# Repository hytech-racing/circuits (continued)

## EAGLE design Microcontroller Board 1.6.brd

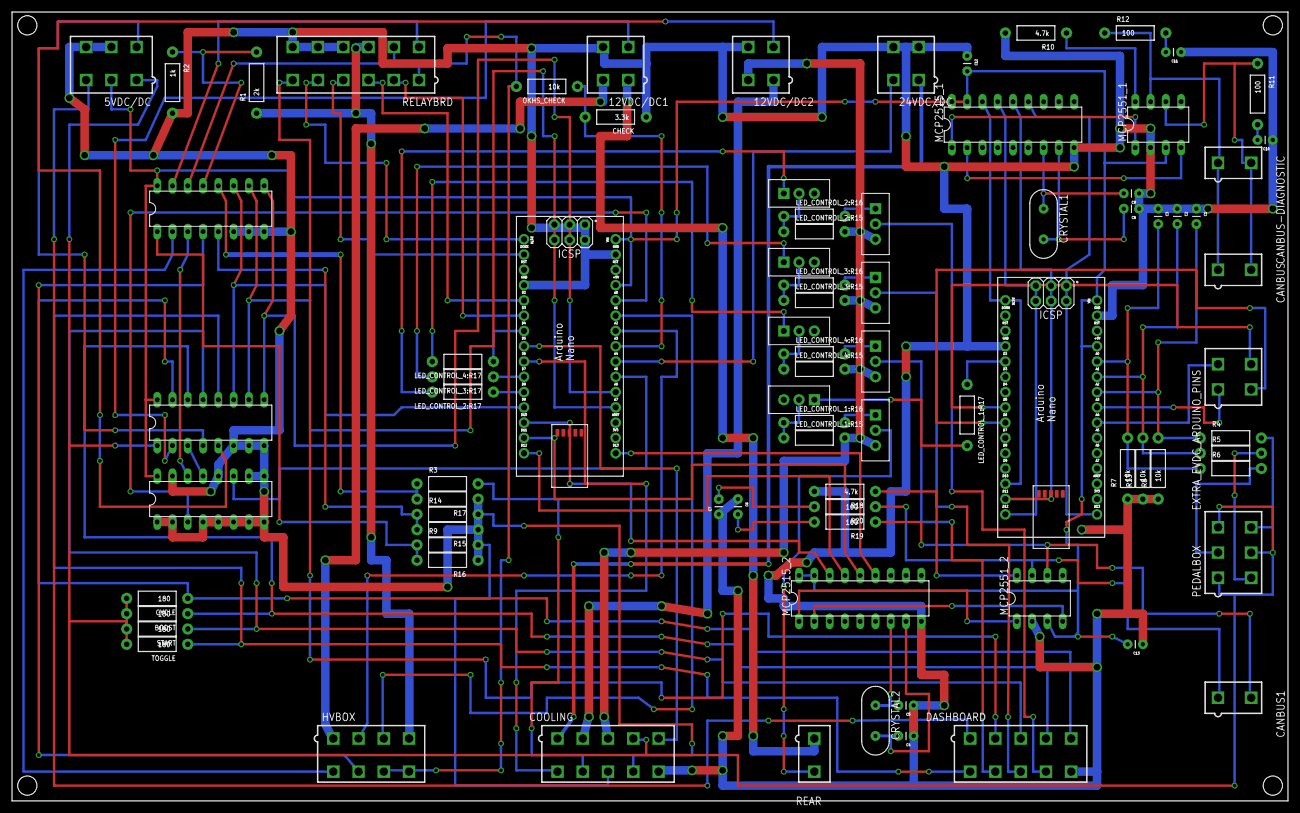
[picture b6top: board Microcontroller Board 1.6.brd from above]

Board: 2 copper layers, 212.1 x 131.1 mm, 84 parts (0 on the bottom side), 103 nets.

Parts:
5VDC/DC: 5566-6
12VDC/DC1, 12VDC/DC2, 24VDC/DC: 5566-4
16_CHANNEL_MULTIPLEXER:MULTIPLEXER_1, 16_CHANNEL_MULTIPLEXER:MULTIPLEXER_2, 16_CHANNEL_MULTIPLEXER:MULTIPLEXER_3: CD74HC4051E; DIL16
BOOST: 180; AXIAL-0.4
C1, C2, C3: CAP-PTH-SMALL
C4, C5, C8, C9: 22pF; CAP-PTH-SMALL
C6, C7, C10, C11: 560pF; CAP-PTH-SMALL
C12, C13: 0.1uF; CAP-PTH-SMALL
CANBUS, CANBUS1: 5566-2
CANBUS-DIAGNOSTIC: 5566-2
CHECK: 3.3k; AXIAL-0.4
COOLING: 5566-10
CRYSTAL1, CRYSTAL2: 16MHz; HC49US
CYCLE: 180; AXIAL-0.4
DASHBOARD: 5566-10
EXTRA_EVDC_ARDUINO_PINS: 5566-4
HVBOX: 5566-8
LED_CONTROL_1:NPN1, LED_CONTROL_2:NPN1, LED_CONTROL_3:NPN1, LED_CONTROL_4:NPN1: TO-220
LED_CONTROL_1:PNP1, LED_CONTROL_2:PNP1, LED_CONTROL_3:PNP1, LED_CONTROL_4:PNP1: BJT_PNP; TO-220
LED_CONTROL_1:R15, LED_CONTROL_1:R16, LED_CONTROL_1:R17, LED_CONTROL_2:R15, LED_CONTROL_2:R16, LED_CONTROL_2:R17, LED_CONTROL_3:R15, LED_CONTROL_3:R16, LED_CONTROL_3:R17, LED_CONTROL_4:R15, LED_CONTROL_4:R16, LED_CONTROL_4:R17: AXIAL-0.4
MCP2515_1, MCP2515_2: MCP2515; DIL18
MCP2551_1, MCP2551_2: MCP2551; DIL08
OKHS_CHECK: 10k; AXIAL-0.4
PCB1, PCB2: ARDUINO_NANO
PEDALBOX: 5566-6
R1: 2k; AXIAL-0.4
R2: 1k; AXIAL-0.4
R3, R4, R5, R6, R9, R14, R15, R16, R17: AXIAL-0.4
R7, R8, R13: 10k; AXIAL-0.4
R10, R18: 4.7k; AXIAL-0.4
R11, R12, R19, R20: 100; AXIAL-0.4
REAR: 5566-2
RELAYBRD: 5566-12
START: 180; AXIAL-0.4
TOGGLE: 180; AXIAL-0.4

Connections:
5VDC/DC_THERMISTOR: 5VDC/DC.4, 16_CHANNEL_MULTIPLEXER:MULTIPLEXER_2.4
5VSUPPLY1: 5VDC/DC.1, 16_CHANNEL_MULTIPLEXER:MULTIPLEXER_2.1, BOOST.P$2, COOLING.4, CYCLE.P$2, PEDALBOX.1, PEDALBOX.3, PEDALBOX.5, START.P$2, TOGGLE.P$2
5VSUPPLY2: 5VDC/DC.2, 16_CHANNEL_MULTIPLEXER:MULTIPLEXER_1.16, 16_CHANNEL_MULTIPLEXER:MULTIPLEXER_2.16, 16_CHANNEL_MULTIPLEXER:MULTIPLEXER_3.16, C12.2, C13.2, MCP2515_1.17, MCP2515_1.18, MCP2515_2.17, MCP2515_2.18, MCP2551_1.3, MCP2551_2.3, PCB1.5V, PCB1.VIN, PCB2.5V, PCB2.VIN
5VSUPPLY3: 5VDC/DC.3, DASHBOARD.1
12VDC/DC1_THERMISTOR: 12VDC/DC1.3, 16_CHANNEL_MULTIPLEXER:MULTIPLEXER_2.2
12VDC/DC2_THERMISTOR: 12VDC/DC2.3, 16_CHANNEL_MULTIPLEXER:MULTIPLEXER_2.5
12VSUPPLY1: 12VDC/DC1.1, REAR.1
12VSUPPLY2: 12VDC/DC1.2, HVBOX.1
12VSUPPLY3: 12VDC/DC2.1, COOLING.2
12VSUPPLY4: 12VDC/DC2.2, COOLING.3, LED_CONTROL_1:PNP1.3, LED_CONTROL_1:R15.P$2, LED_CONTROL_2:PNP1.3, LED_CONTROL_2:R15.P$2, LED_CONTROL_3:PNP1.3, LED_CONTROL_3:R15.P$2, LED_CONTROL_4:PNP1.3, LED_CONTROL_4:R15.P$2
16_CHANNEL_MULTIPLEXER:N$2: 16_CHANNEL_MULTIPLEXER:MULTIPLEXER_1.14, 16_CHANNEL_MULTIPLEXER:MULTIPLEXER_3.3
16_CHANNEL_MULTIPLEXER:N$4: 16_CHANNEL_MULTIPLEXER:MULTIPLEXER_1.13, 16_CHANNEL_MULTIPLEXER:MULTIPLEXER_2.3
24VDC/DC_THERMISTOR: 24VDC/DC.2, PCB1.A4
24VSUPPLY: 24VDC/DC.1, COOLING.1
AIR_UNREGULATED_DIVIDER: 16_CHANNEL_MULTIPLEXER:MULTIPLEXER_3.15, RELAYBRD.7
A_SIGNAL: PEDALBOX.2, R6.P$2
A_SIGNAL_FILTERED: C3.2, PCB2.A0, R6.P$1, R7.P$2
BMS_FAULT_LED: DASHBOARD.9, LED_CONTROL_2:PNP1.2
BMS_FAULT_LED_CTRL: LED_CONTROL_2:R17.P$1, PCB1.D8
BRAKE_LIGHT_LED: LED_CONTROL_1:PNP1.2, REAR.2
BRAKE_LIGHT_LED_CTRL: LED_CONTROL_1:R17.P$1, PCB2.D2
BTN_BOOST: 16_CHANNEL_MULTIPLEXER:MULTIPLEXER_2.14, BOOST.P$1, DASHBOARD.4
BTN_CYCLE: 16_CHANNEL_MULTIPLEXER:MULTIPLEXER_2.15, CYCLE.P$1, DASHBOARD.5
BTN_START: 16_CHANNEL_MULTIPLEXER:MULTIPLEXER_2.13, DASHBOARD.3, START.P$1
BTN_TOGGLE: 16_CHANNEL_MULTIPLEXER:MULTIPLEXER_2.12, DASHBOARD.6, TOGGLE.P$1
B_SIGNAL: PEDALBOX.4, R5.P$2
B_SIGNAL_FILTERED: C2.2, PCB2.A1, R5.P$1, R13.P$2
CAN-H_1: CANBUS.1, CANBUS-DIAGNOSTIC.1, MCP2551_1.7, R12.P$1
CAN-H_2: CANBUS1.1, MCP2551_2.7, R20.P$1
CAN-L_1: CANBUS.2, CANBUS-DIAGNOSTIC.2, MCP2551_1.6, R11.P$1
CAN-L_2: CANBUS1.2, MCP2551_2.6, R19.P$1
CONTROL_10: HVBOX.2, PCB1.A2
CONTROL_11: HVBOX.3, PCB1.A1
COOLING_SENSOR_1: 16_CHANNEL_MULTIPLEXER:MULTIPLEXER_3.12, R3.P$1, R17.P$2
COOLING_SENSOR_2: 16_CHANNEL_MULTIPLEXER:MULTIPLEXER_3.1, R9.P$1, R16.P$2
COOLING_SENSOR_3: 16_CHANNEL_MULTIPLEXER:MULTIPLEXER_3.5, R14.P$1, R15.P$2
C_SIGNAL: PEDALBOX.6, R4.P$2
C_SIGNAL_FILTERED: C1.2, PCB2.A2, R4.P$1, R8.P$2
EVDC_ANALOG_1: EXTRA_EVDC_ARDUINO_PINS.1, PCB2.A3
EVDC_ANALOG_2: EXTRA_EVDC_ARDUINO_PINS.2, PCB2.A4
EVDC_DIGITAL_1: EXTRA_EVDC_ARDUINO_PINS.3, PCB2.D6
EVDC_DIGITAL_2: EXTRA_EVDC_ARDUINO_PINS.4, PCB2.D5
FAN_CTRL: COOLING.5, PCB1.D5
GND: 5VDC/DC.5, 5VDC/DC.6, 12VDC/DC1.4, 12VDC/DC2.4, 16_CHANNEL_MULTIPLEXER:MULTIPLEXER_1.1, 16_CHANNEL_MULTIPLEXER:MULTIPLEXER_1.2, 16_CHANNEL_MULTIPLEXER:MULTIPLEXER_1.4, 16_CHANNEL_MULTIPLEXER:MULTIPLEXER_1.5, 16_CHANNEL_MULTIPLEXER:MULTIPLEXER_1.6, 16_CHANNEL_MULTIPLEXER:MULTIPLEXER_1.7, 16_CHANNEL_MULTIPLEXER:MULTIPLEXER_1.8, 16_CHANNEL_MULTIPLEXER:MULTIPLEXER_1.9, 16_CHANNEL_MULTIPLEXER:MULTIPLEXER_1.10, 16_CHANNEL_MULTIPLEXER:MULTIPLEXER_1.12, 16_CHANNEL_MULTIPLEXER:MULTIPLEXER_1.15, 16_CHANNEL_MULTIPLEXER:MULTIPLEXER_2.6, 16_CHANNEL_MULTIPLEXER:MULTIPLEXER_2.7, 16_CHANNEL_MULTIPLEXER:MULTIPLEXER_2.8, 16_CHANNEL_MULTIPLEXER:MULTIPLEXER_3.6, 16_CHANNEL_MULTIPLEXER:MULTIPLEXER_3.7, 16_CHANNEL_MULTIPLEXER:MULTIPLEXER_3.8, 24VDC/DC.3, 24VDC/DC.4, C1.1, C2.1, C3.1, C4.1, C5.1, C6.1, C7.1, C8.1, C9.1, C10.1, C11.1, C12.1, C13.1, CHECK.P$1, COOLING.10, DASHBOARD.10, MCP2515_1.9, MCP2515_2.9, MCP2551_1.2, MCP2551_2.2, PCB1.GND, PCB1.GND., PCB2.GND, PCB2.GND., R2.P$2, R7.P$1, R8.P$1, R10.P$2, R13.P$1, R15.P$1, R16.P$1, R17.P$1, R18.P$2, RELAYBRD.10, RELAYBRD.11, RELAYBRD.12
IMD_FAULT_LED: DASHBOARD.8, LED_CONTROL_3:PNP1.2
IMD_FAULT_LED_CTRL: LED_CONTROL_3:R17.P$1, PCB1.D7
LED_CONTROL_1:N$24: LED_CONTROL_1:NPN1.1, LED_CONTROL_1:R17.P$2
LED_CONTROL_1:N$25: LED_CONTROL_1:NPN1.2, LED_CONTROL_1:R15.P$1, LED_CONTROL_1:R16.P$1
LED_CONTROL_1:N$27: LED_CONTROL_1:PNP1.1, LED_CONTROL_1:R16.P$2
LED_CONTROL_2:N$24: LED_CONTROL_2:NPN1.1, LED_CONTROL_2:R17.P$2
LED_CONTROL_2:N$25: LED_CONTROL_2:NPN1.2, LED_CONTROL_2:R15.P$1, LED_CONTROL_2:R16.P$1
LED_CONTROL_2:N$27: LED_CONTROL_2:PNP1.1, LED_CONTROL_2:R16.P$2
LED_CONTROL_3:N$24: LED_CONTROL_3:NPN1.1, LED_CONTROL_3:R17.P$2
LED_CONTROL_3:N$25: LED_CONTROL_3:NPN1.2, LED_CONTROL_3:R15.P$1, LED_CONTROL_3:R16.P$1
LED_CONTROL_3:N$27: LED_CONTROL_3:PNP1.1, LED_CONTROL_3:R16.P$2
LED_CONTROL_4:N$24: LED_CONTROL_4:NPN1.1, LED_CONTROL_4:R17.P$2
LED_CONTROL_4:N$25: LED_CONTROL_4:NPN1.2, LED_CONTROL_4:R15.P$1, LED_CONTROL_4:R16.P$1
LED_CONTROL_4:N$27: LED_CONTROL_4:PNP1.1, LED_CONTROL_4:R16.P$2
MCP2515-MISO_1: MCP2515_1.15, PCB2.D12
MCP2515-MISO_2: MCP2515_2.15, PCB1.D12
MCP2515-MOSI_1: MCP2515_1.14, PCB2.D11
MCP2515-MOSI_2: MCP2515_2.14, PCB1.D11
MCP2515-SCK_1: MCP2515_1.13, PCB2.D13
MCP2515-SCK_2: MCP2515_2.13, PCB1.D13
MCP2515-SS_1: MCP2515_1.16, PCB2.D10
MCP2515-SS_2: MCP2515_2.16, PCB1.D10
unnamed: 16_CHANNEL_MULTIPLEXER:MULTIPLEXER_1.3, PCB1.A0
unnamed: COOLING.7, R3.P$2
unnamed: COOLING.8, R9.P$2
unnamed: COOLING.9, R14.P$2
unnamed: MCP2515_2.1, MCP2551_2.1
unnamed: MCP2515_2.2, MCP2551_2.4
unnamed: C4.2, CRYSTAL2.2, MCP2515_2.8
unnamed: 16_CHANNEL_MULTIPLEXER:MULTIPLEXER_1.11, PCB1.A5
unnamed: 16_CHANNEL_MULTIPLEXER:MULTIPLEXER_2.11, 16_CHANNEL_MULTIPLEXER:MULTIPLEXER_3.11, PCB1.D9
unnamed: C8.2, CRYSTAL1.2, MCP2515_1.8
unnamed: MCP2515_1.1, MCP2551_1.1
unnamed: MCP2515_1.2, MCP2551_1.4
unnamed: C11.2, R12.P$2
unnamed: C9.2, CRYSTAL1.1, MCP2515_1.7
unnamed: MCP2551_1.8, R10.P$1
unnamed: C10.2, R11.P$2
unnamed: CHECK.P$2, OKHS_CHECK.P$1, PCB1.A3
unnamed: MCP2551_2.8, R18.P$1
unnamed: C5.2, CRYSTAL2.1, MCP2515_2.7
unnamed: C7.2, R20.P$2
unnamed: C6.2, R19.P$2
unnamed: 16_CHANNEL_MULTIPLEXER:MULTIPLEXER_2.9, 16_CHANNEL_MULTIPLEXER:MULTIPLEXER_3.9, PCB1.A6
unnamed: 16_CHANNEL_MULTIPLEXER:MULTIPLEXER_2.10, 16_CHANNEL_MULTIPLEXER:MULTIPLEXER_3.10, PCB1.A7
OKHS_IN: HVBOX.7, OKHS_CHECK.P$2, RELAYBRD.1
PUMP_CTRL: COOLING.6, PCB1.D6
PWM_HIGH: 16_CHANNEL_MULTIPLEXER:MULTIPLEXER_3.4, HVBOX.6
PWM_LOW: 16_CHANNEL_MULTIPLEXER:MULTIPLEXER_3.2, HVBOX.5
READY_DRIVE_CTRL: PCB1.RX1, RELAYBRD.4
READY_SOUND: DASHBOARD.2, RELAYBRD.6
RELAYBRD_THERMISTOR: 16_CHANNEL_MULTIPLEXER:MULTIPLEXER_3.14, RELAYBRD.8
SOFTWARE_DC/DC_CTRL: PCB1.TX1, RELAYBRD.5
SOFTWARE_PUSHBUTTON_CTRL: PCB1.D3, RELAYBRD.2
SOFTWARE_SHUTDOWN_CTRL: PCB1.D2, RELAYBRD.3
START_LED: DASHBOARD.7, LED_CONTROL_4:PNP1.2
START_LED_CTRL: LED_CONTROL_4:R17.P$1, PCB1.D4
VCCAIR: HVBOX.4, R1.P$1, RELAYBRD.9
VCC_AIR_DIVIDER: 16_CHANNEL_MULTIPLEXER:MULTIPLEXER_3.13, R1.P$2, R2.P$1

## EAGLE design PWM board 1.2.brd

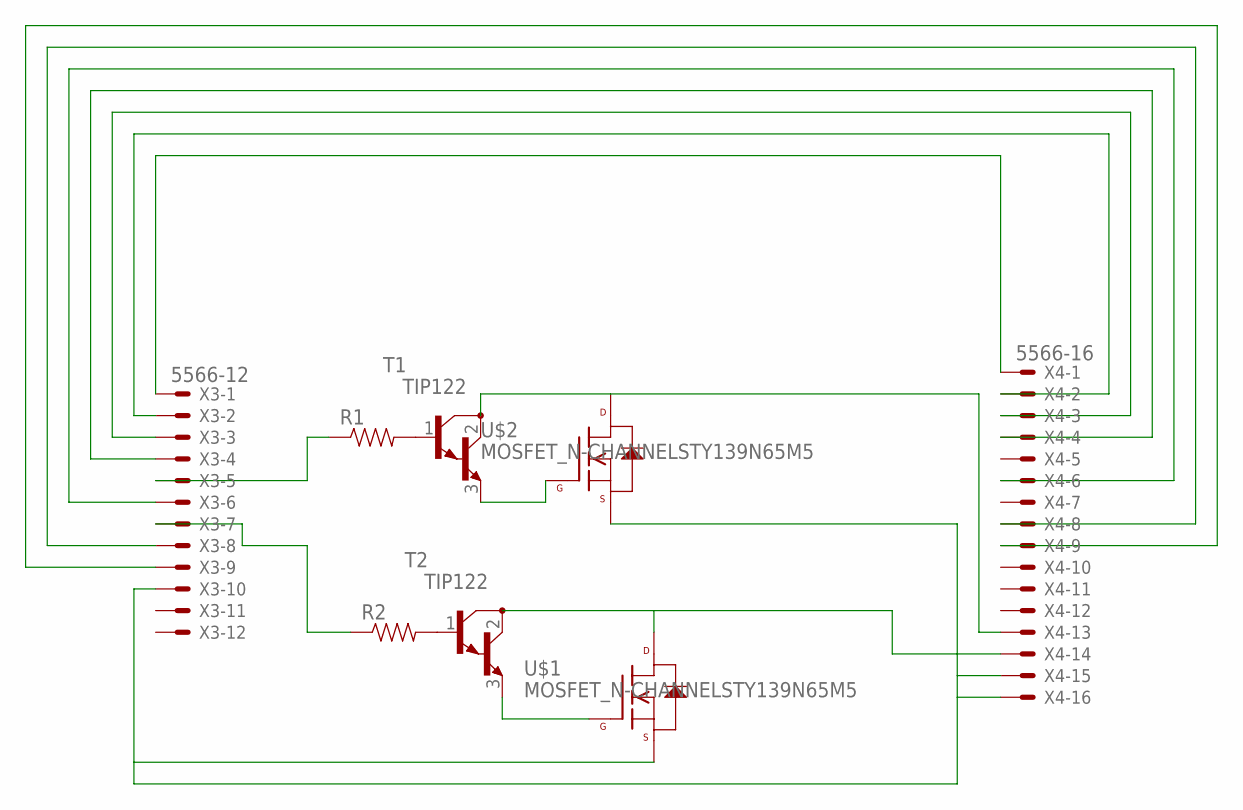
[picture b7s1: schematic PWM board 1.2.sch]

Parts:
R1, R2: RESISTORPTH-1/2W; AXIAL-0.5
T1, T2: TIP122; TO220
U$1, U$2: MOSFET_N-CHANNELSTY139N65M5; TO-264_MAX247
X3: 5566-12
X4: 5566-16

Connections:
unnamed: T1.2 (C), U$2.P2 (DRAIN), X4.13
unnamed: T2.2 (C), U$1.P2 (DRAIN), X4.14
unnamed: T2.3 (E), U$1.P1 (GATE)
unnamed: T1.3 (E), U$2.P1 (GATE)
unnamed: R1.P$2 (2), T1.1 (B)
unnamed: R2.P$2 (2), T2.1 (B)
unnamed: R1.P$1 (1), X3.5
unnamed: R2.P$1 (1), X3.7
unnamed: X3.1, X4.1
unnamed: X3.2, X4.2
unnamed: X3.3, X4.3
unnamed: X3.4, X4.4
unnamed: U$1.P3 (SOURCE), U$2.P3 (SOURCE), X3.10, X4.15, X4.16
unnamed: X3.6, X4.6
unnamed: X3.8, X4.8
unnamed: X3.9, X4.9

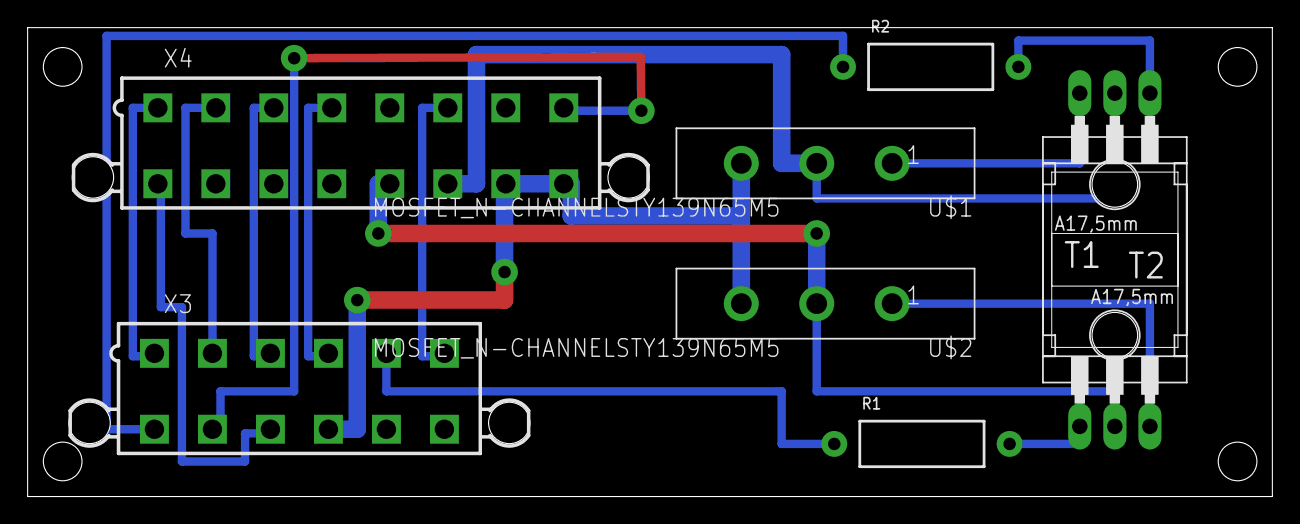
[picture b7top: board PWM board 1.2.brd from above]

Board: 2 copper layers, 90.2 x 34.0 mm, 8 parts (0 on the bottom side), 16 nets.

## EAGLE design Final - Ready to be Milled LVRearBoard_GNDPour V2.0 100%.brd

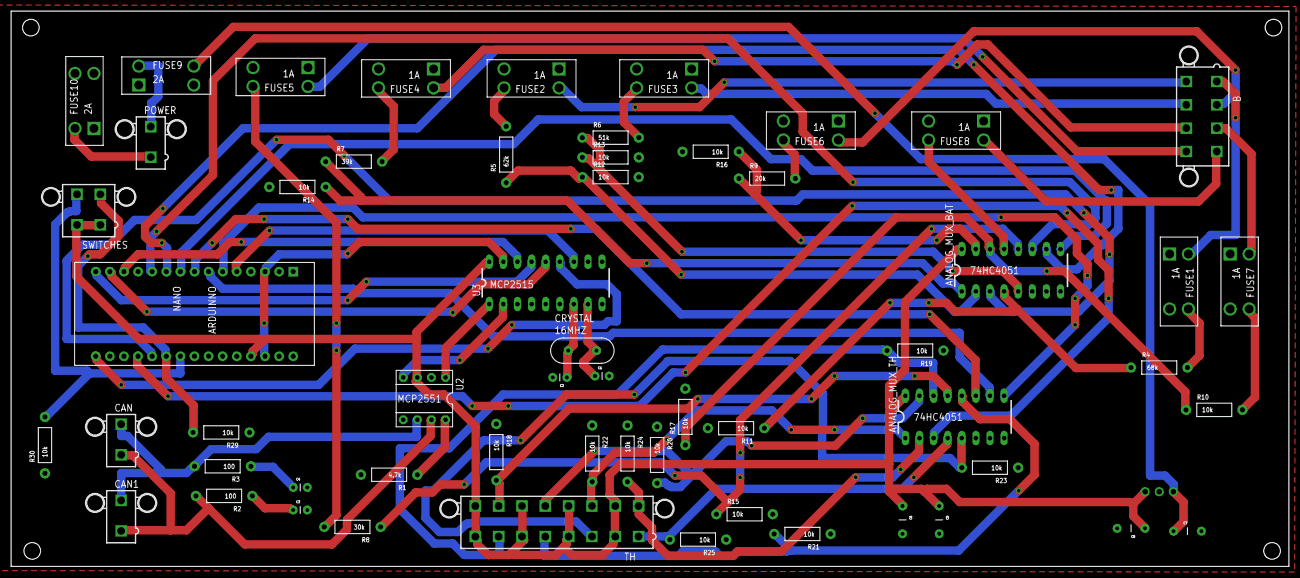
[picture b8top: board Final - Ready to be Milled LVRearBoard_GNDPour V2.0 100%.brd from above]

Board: 2 copper layers, 230.1 x 100.0 mm, 58 parts (1 on the bottom side), 61 nets.

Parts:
ANALOG_MUX_BAT: 74HC4051; DIL16
ANALOG_MUX_TH: 74HC4051; DIL16
ARDUINNO: NANO; ARDUINO-NANO
B: 5566-8
C1, C2: 22pF; CAP-PTH-SMALL
C3, C4: 560pF; CAP-PTH-SMALL
C5, C6: 0.1uF; CAP-PTH-5MM
C7, C8: CAP-PTH-5MM
CAN, CAN1: 5566-2
CRYSTAL: 16MHZ; HC49US
DC/DC: 24-5V; SIP3
FUSE1, FUSE2, FUSE3, FUSE4, FUSE5, FUSE6, FUSE7, FUSE8: 1A; KEYSTONE3568
FUSE9, FUSE10: 2A; KEYSTONE3568
POWER: 5566-2
R1: 4.7k; AXIAL-0.4
R2, R3: 100; AXIAL-0.4
R4: 68k; AXIAL-0.4
R5: 62k; AXIAL-0.4
R6: 51k; AXIAL-0.4
R7: 39k; AXIAL-0.4
R8: 30k; AXIAL-0.4
R9: 20k; AXIAL-0.4
R10, R11, R12, R13, R14, R15, R16, R17, R18, R19, R20, R21, R22, R23, R24, R25, R29, R30: 10k; AXIAL-0.4
SWITCHES: 5566-4
TH: 5566-16
U2: MCP2551; DIL08
U3: MCP2515; DIL18

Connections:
5V: ANALOG_MUX_BAT.16, ANALOG_MUX_TH.16, ARDUINNO.27, C5.1, C6.1, C8.1, DC/DC.3, SWITCHES.1, SWITCHES.2, TH.2, TH.4, TH.6, TH.8, TH.10, TH.12, TH.14, TH.16, U2.3, U3.18
ANALOG_BAT: ANALOG_MUX_BAT.3, ARDUINNO.20
ANALOG_TH: ANALOG_MUX_TH.3, ARDUINNO.19
A_BAT: ANALOG_MUX_BAT.11, ARDUINNO.11
A_TH: ANALOG_MUX_TH.11, ARDUINNO.8
B3: ANALOG_MUX_BAT.13, FUSE8.2A
B6: ANALOG_MUX_BAT.14, R10.P$1, R17.P$1
B9: ANALOG_MUX_BAT.15, R9.P$1, R16.P$1
B12: ANALOG_MUX_BAT.12, R8.P$1, R15.P$1
B15: ANALOG_MUX_BAT.1, R7.P$1, R14.P$1
B18: ANALOG_MUX_BAT.5, R6.P$1, R13.P$1
B21: ANALOG_MUX_BAT.2, R5.P$1, R12.P$1
B24: ANALOG_MUX_BAT.4, R4.P$1, R11.P$1
BMS: ARDUINNO.22, R30.P$2, SWITCHES.4
B_BAT: ANALOG_MUX_BAT.10, ARDUINNO.10
B_TH: ANALOG_MUX_TH.10, ARDUINNO.7
CANH: CAN.1, CAN1.1, R2.P$2, U2.7
CANL: CAN.2, CAN1.2, R3.P$2, U2.6
CAN_CS: ARDUINNO.13, U3.16
CAN_INT: ARDUINNO.5, U3.12
CAN_TX: U2.1, U3.1
C_BAT: ANALOG_MUX_BAT.9, ARDUINNO.9
C_TH: ANALOG_MUX_TH.9, ARDUINNO.6
GND: ANALOG_MUX_BAT.6, ANALOG_MUX_BAT.7, ANALOG_MUX_BAT.8, ANALOG_MUX_TH.6, ANALOG_MUX_TH.7, ANALOG_MUX_TH.8, ARDUINNO.4, ARDUINNO.29, C1.2, C2.2, C3.2, C4.2, C5.2, C6.2, C7.2, C8.2, DC/DC.2, FUSE10.2A, R1.P$2, R11.P$2, R12.P$2, R13.P$2, R14.P$2, R15.P$2, R16.P$2, R17.P$2, R18.P$1, R19.P$1, R20.P$1, R21.P$1, R22.P$1, R23.P$1, R24.P$1, R25.P$1, R29.P$1, R30.P$1, U2.2, U3.9
IMD: ARDUINNO.21, R29.P$2, SWITCHES.3
MISO: ARDUINNO.15, U3.15
MOSI: ARDUINNO.14, U3.14
unnamed: FUSE9.1A, POWER.2
unnamed: C3.1, R2.P$1
unnamed: B.8, FUSE5.1A
unnamed: C2.1, CRYSTAL.1, U3.7
unnamed: C4.1, R3.P$1
unnamed: B.7, FUSE4.1A
unnamed: C7.1, DC/DC.1, FUSE9.2A
unnamed: FUSE2.2A, R5.P$2
unnamed: FUSE1.2A, R4.P$2
unnamed: FUSE3.2A, R6.P$2
unnamed: FUSE4.2A, R7.P$2
unnamed: FUSE5.2A, R8.P$2
unnamed: FUSE6.2A, R9.P$2
unnamed: FUSE7.2A, R10.P$2
unnamed: B.6, FUSE3.1A
unnamed: B.5, FUSE2.1A
unnamed: B.1, FUSE1.1A
unnamed: B.2, FUSE6.1A
unnamed: B.3, FUSE7.1A
unnamed: B.4, FUSE8.1A
unnamed: FUSE10.1A, POWER.1
unnamed: U2.4, U3.2
OSC1: C1.1, CRYSTAL.2, U3.8
RS: ARDUINNO.3, ARDUINNO.28, U3.17
RS$: R1.P$1, U2.8
SCK: ARDUINNO.16, U3.13
TH1: ANALOG_MUX_TH.13, R18.P$2, TH.15
TH2: ANALOG_MUX_TH.14, R19.P$2, TH.7
TH3: ANALOG_MUX_TH.15, R20.P$2, TH.13
TH4: ANALOG_MUX_TH.12, R21.P$2, TH.5
TH5: ANALOG_MUX_TH.1, R22.P$2, TH.11
TH6: ANALOG_MUX_TH.5, R23.P$2, TH.3
TH7: ANALOG_MUX_TH.2, R24.P$2, TH.9
TH8: ANALOG_MUX_TH.4, R25.P$2, TH.1

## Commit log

2016-09-05 Final versions of 2016 vehicle electronic control boards
